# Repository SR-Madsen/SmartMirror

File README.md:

# SmartMirror
This project contains the KiCad and programming files used for a Smart Mirror project running Embedded Linux. The project is based on a microprocessor showing graphics and gathering data for showing information like weather and time.

## Project Structure
A block diagram of the project is shown in the figure below.

## Hardware
The hardware is based on the iMX6ULL microprocessor from NXP, with the design and PCB made myself, but inspired by evaluation kits.

## Software
The NXP Pins Tool is used for setting up the microprocessor. NXP's Embedded Linux tools are used for configuring the software.

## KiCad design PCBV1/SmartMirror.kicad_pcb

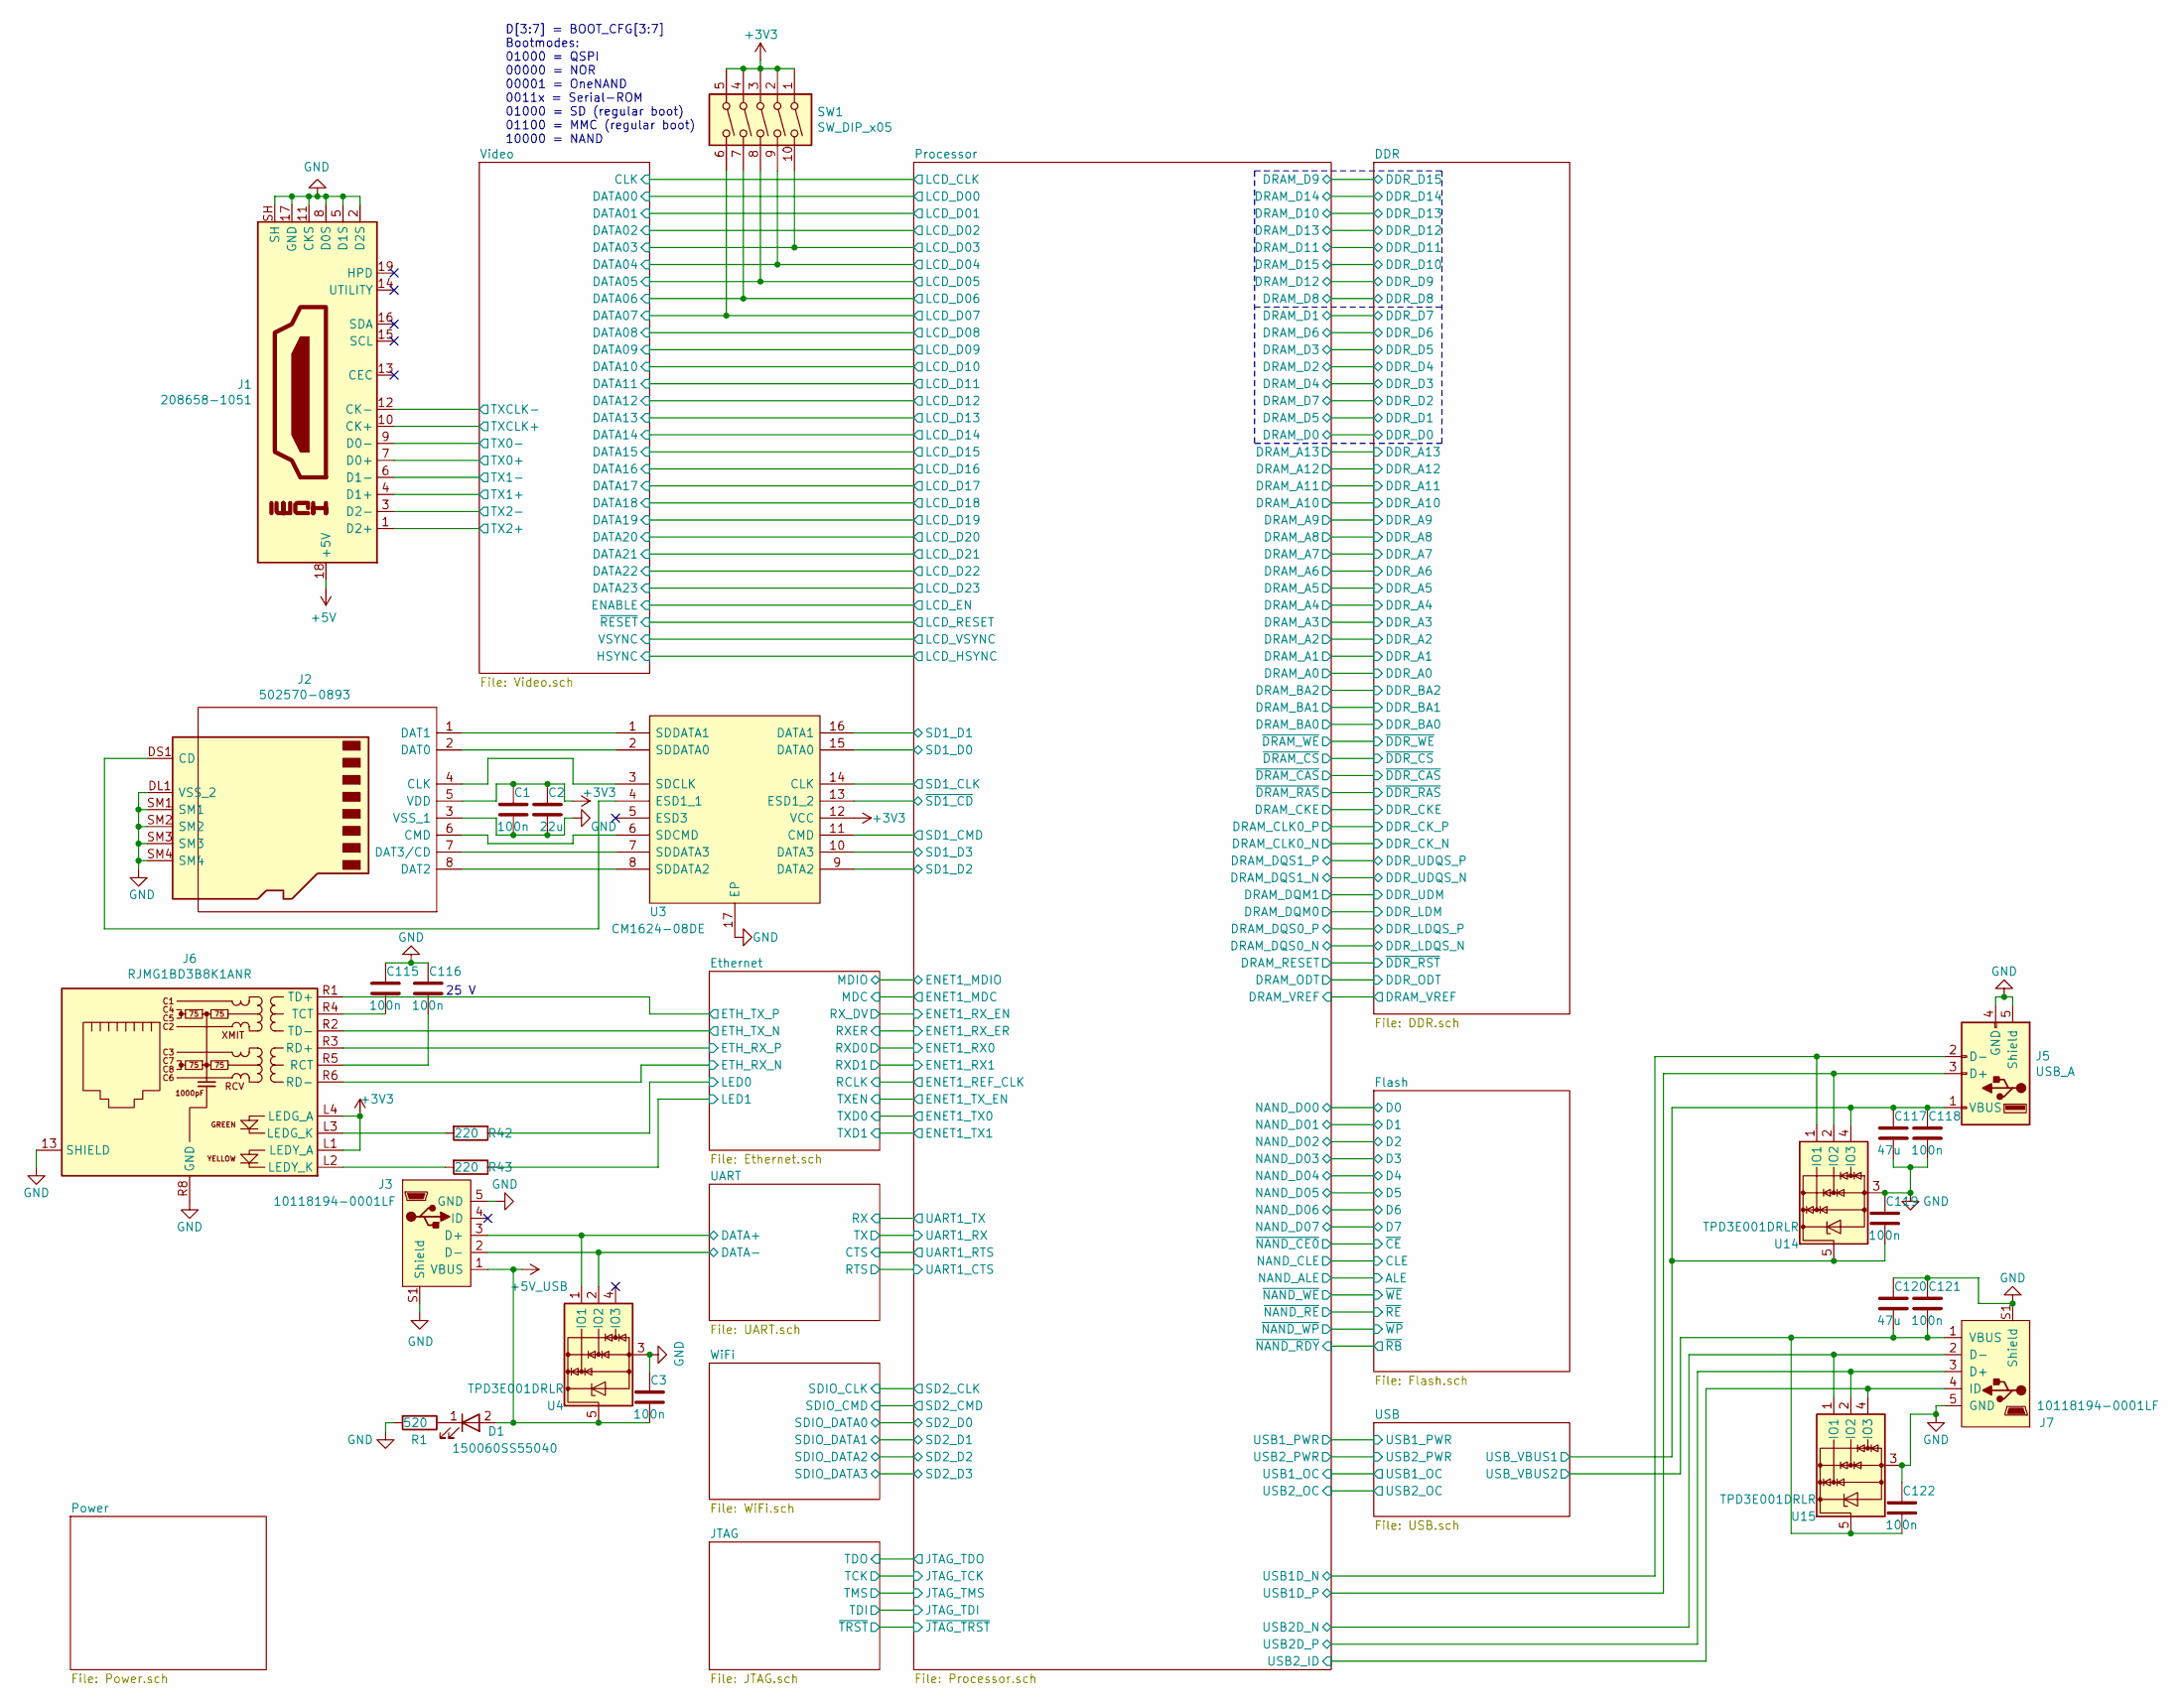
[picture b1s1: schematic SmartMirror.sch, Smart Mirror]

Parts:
C1, C3, C115, C116, C118, C119, C121, C122: 100n; C_0603_1608Metric
C2: 22u; C_0603_1608Metric
C117, C120: 47u; C_0805_2012Metric
D1: 150060SS55040; Mouser Part Number 710-150060SS55040
J1: 208658-1051; 2086581051
J2: 502570-0893
J3, J7: 10118194-0001LF
J5: USB_A; USB_A_Molex_67643_Horizontal
J6: RJMG1BD3B8K1ANR
R1: 520; R_0603_1608Metric
R42, R43: 220; R_0603_1608Metric
SW1: SW_DIP_x05; SW_DIP_SPSTx05_Slide_6.7x14.26mm_W6.73mm_P2.54mm_LowProfile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
U3: CM1624-08DE; CM1624
U4, U14, U15: TPD3E001DRLR; SOT-553

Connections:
+3V3: C1.1, C2.1, J2.5 (VDD), J6.L1 (LEDY_A), J6.L4 (LEDG_A), SW1.1, SW1.2, SW1.3, SW1.4, SW1.5, U3.12 (VCC); also elsewhere on the board
+5V: J1.18 (+5V); also elsewhere on the board
+5V_USB: C3.2, D1.2 (A), J3.1 (VBUS), U4.5; also elsewhere on the board
/Ethernet/ETH_RX_N: J6.R6 (RD-); also elsewhere on the board
/Ethernet/ETH_RX_P: J6.R3 (RD+); also elsewhere on the board
/Ethernet/ETH_TX_N: J6.R2 (TD-); also elsewhere on the board
/Ethernet/ETH_TX_P: J6.R1 (TD+); also elsewhere on the board
/Ethernet/LED0: R42.1; also elsewhere on the board
/Ethernet/LED1: R43.1; also elsewhere on the board
/Processor/SD1_CLK: U3.14 (CLK); also elsewhere on the board
/Processor/SD1_CMD: U3.11 (CMD); also elsewhere on the board
/Processor/SD1_D0: U3.15 (DATA0); also elsewhere on the board
/Processor/SD1_D1: U3.16 (DATA1); also elsewhere on the board
/Processor/SD1_D2: U3.9 (DATA2); also elsewhere on the board
/Processor/SD1_D3: U3.10 (DATA3); also elsewhere on the board
/Processor/USB1D_N: J5.2 (D-), U14.1 (IO1); also elsewhere on the board
/Processor/USB1D_P: J5.3 (D+), U14.2 (IO2); also elsewhere on the board
/Processor/USB2D_N: J7.2 (D-), U15.1 (IO1); also elsewhere on the board
/Processor/USB2D_P: J7.3 (D+), U15.2 (IO2); also elsewhere on the board
/Processor/USB2_ID: J7.4 (ID), U15.4 (IO3); also elsewhere on the board
/Processor/~SD1_CD: U3.13 (ESD1_2); also elsewhere on the board
/UART/DATA+: J3.3 (D+), U4.1 (IO1); also elsewhere on the board
/UART/DATA-: J3.2 (D-), U4.2 (IO2); also elsewhere on the board
/USB/USB_VBUS1: C117.1, C118.1, C119.2, J5.1 (VBUS), U14.4 (IO3), U14.5; also elsewhere on the board
/USB/USB_VBUS2: C120.2, C121.2, C122.2, J7.1 (VBUS), U15.5; also elsewhere on the board
/Video/DATA03: SW1.10; also elsewhere on the board
/Video/DATA04: SW1.9; also elsewhere on the board
/Video/DATA05: SW1.8; also elsewhere on the board
/Video/DATA06: SW1.7; also elsewhere on the board
/Video/DATA07: SW1.6; also elsewhere on the board
/Video/TX0+: J1.7 (D0+); also elsewhere on the board
/Video/TX0-: J1.9 (D0-); also elsewhere on the board
/Video/TX1+: J1.4 (D1+); also elsewhere on the board
/Video/TX1-: J1.6 (D1-); also elsewhere on the board
/Video/TX2+: J1.1 (D2+); also elsewhere on the board
/Video/TX2-: J1.3 (D2-); also elsewhere on the board
/Video/TXCLK+: J1.10 (CK+); also elsewhere on the board
/Video/TXCLK-: J1.12 (CK-); also elsewhere on the board
GND: C1.2, C2.2, C3.1, C115.1, C116.1, C117.2, C118.2, C119.1, C120.1, C121.1, C122.1, J1.2 (D2S), J1.5 (D1S), J1.8 (D0S), J1.11 (CKS), J1.17 (GND), J1.SH, J2.3 (VSS_1), J2.DL1 (VSS_2), J2.SM1, J2.SM2, J2.SM3, J2.SM4, J3.5 (GND), J3.S1 (Shield), J5.4 (GND), J5.5 (Shield), J6.13 (SHIELD), J6.R8 (GND), J7.5 (GND), J7.S1 (Shield), R1.2, U3.17 (EP), U4.3, U14.3, U15.3; also elsewhere on the board
unnamed: C115.2, J6.R4 (TCT)
unnamed: C116.2, J6.R5 (RCT)
unnamed: D1.1 (K), R1.1
unnamed: J2.1 (DAT1), U3.1 (SDDATA1)
unnamed: J2.2 (DAT0), U3.2 (SDDATA0)
unnamed: J2.4 (CLK), U3.3 (SDCLK)
unnamed: J2.6 (CMD), U3.6 (SDCMD)
unnamed: J2.7 (DAT3/CD), U3.7 (SDDATA3)
unnamed: J2.8 (DAT2), U3.8 (SDDATA2)
unnamed: J2.DS1 (CD), U3.4 (ESD1_1)
unnamed: J6.L2 (LEDY_K), R43.2
unnamed: J6.L3 (LEDG_K), R42.2

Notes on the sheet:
D[3:7] = BOOT_CFG[3:7] Bootmodes: 01000 = QSPI 00000 = NOR 00001 = OneNAND 0011x = Serial-ROM 01000 = SD (regular boot) 01100 = MMC (regular boot) 10000 = NAND
25 V

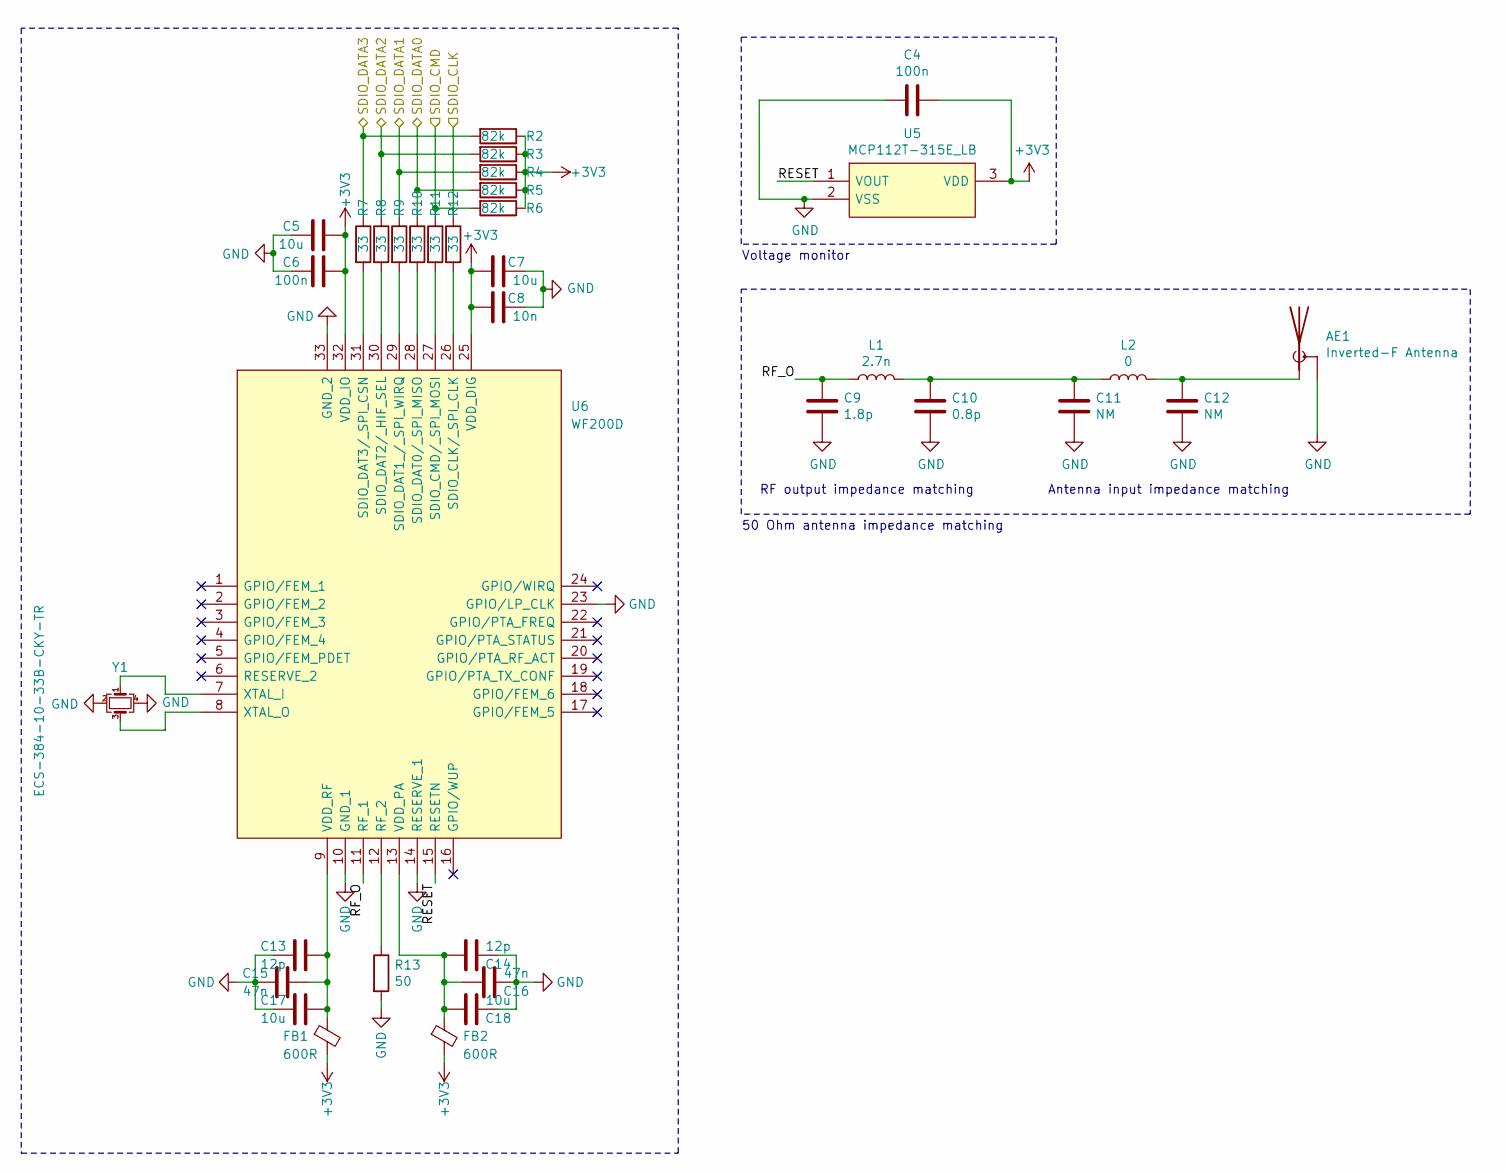
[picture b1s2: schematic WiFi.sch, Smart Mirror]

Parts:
AE1: Inverted-F Antenna; Texas_SWRA117D_2.4GHz_Left
C4, C6: 100n; C_0603_1608Metric
C5, C7, C17, C18: 10u; C_0603_1608Metric
C8: 10n; C_0603_1608Metric
C9: 1.8p; C_0402_1005Metric
C10: 0.8p; C_0402_1005Metric
C11, C12: NM; C_0402_1005Metric
C13, C14: 12p; C_0603_1608Metric
C15, C16: 47n; C_0603_1608Metric
FB1, FB2: 600R; L_0603_1608Metric
L1: 2.7n; L_0402_1005Metric
L2: 0; L_0402_1005Metric
R2, R3, R4, R5, R6: 82k; R_0603_1608Metric
R7, R8, R9, R10, R11, R12: 33; R_0603_1608Metric
R13: 50; R_0603_1608Metric
U5: MCP112T-315E_LB; MCP112T-315E-LB; Manufacturer_Part_Number MCP112T-315E/LB; Mouser Part Number 579-MCP112T-315E/LB
U6: WF200D
Y1: ECS-384-10-33B-CKY-TR; ECS3841033BCKYTR

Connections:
+3V3: C4.1, C5.1, C6.1, C7.2, C8.2, FB1.2, FB2.2, R2.1, R3.1, R4.1, R5.1, R6.1, U5.3 (VDD), U6.25 (VDD_DIG), U6.32 (VDD_IO); also elsewhere on the board
/Processor/SD2_CLK: R12.1; also elsewhere on the board
/Processor/SD2_CMD: R6.2, R11.1; also elsewhere on the board
/Processor/SD2_D0: R5.2, R10.1; also elsewhere on the board
/Processor/SD2_D1: R4.2, R9.1; also elsewhere on the board
/Processor/SD2_D2: R3.2, R8.1; also elsewhere on the board
/Processor/SD2_D3: R2.2, R7.1; also elsewhere on the board
/WiFi/RESET: U5.1 (VOUT), U6.15 (RESETN)
/WiFi/RF_O: C9.1, L1.1, U6.11 (RF_1)
GND: AE1.2 (Shield), C4.2, C5.2, C6.2, C7.1, C8.1, C9.2, C10.2, C11.2, C12.2, C13.2, C14.2, C15.2, C16.2, C17.2, C18.2, R13.2, U5.2 (VSS), U6.10 (GND_1), U6.14 (RESERVE_1), U6.23 (GPIO/LP_CLK), U6.33 (GND_2), Y1.2, Y1.4; also elsewhere on the board
unnamed: AE1.1 (A), C12.1, L2.2
unnamed: C10.1, C11.1, L1.2, L2.1
unnamed: C13.1, C15.1, C17.1, FB1.1, U6.9 (VDD_RF)
unnamed: C14.1, C16.1, C18.1, FB2.1, U6.13 (VDD_PA)
unnamed: R7.2, U6.31 (SDIO_DAT3/_SPI_CSN)
unnamed: R8.2, U6.30 (SDIO_DAT2/_HIF_SEL)
unnamed: R9.2, U6.29 (SDIO_DAT1_/_SPI_WIRQ)
unnamed: R10.2, U6.28 (SDIO_DAT0/_SPI_MISO)
unnamed: R11.2, U6.27 (SDIO_CMD/_SPI_MOSI)
unnamed: R12.2, U6.26 (SDIO_CLK/_SPI_CLK)
unnamed: R13.1, U6.12 (RF_2)
unnamed: U6.7 (XTAL_I), Y1.1
unnamed: U6.8 (XTAL_O), Y1.3

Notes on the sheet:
Voltage monitor
RF output impedance matching
Antenna input impedance matching
50 Ohm antenna impedance matching

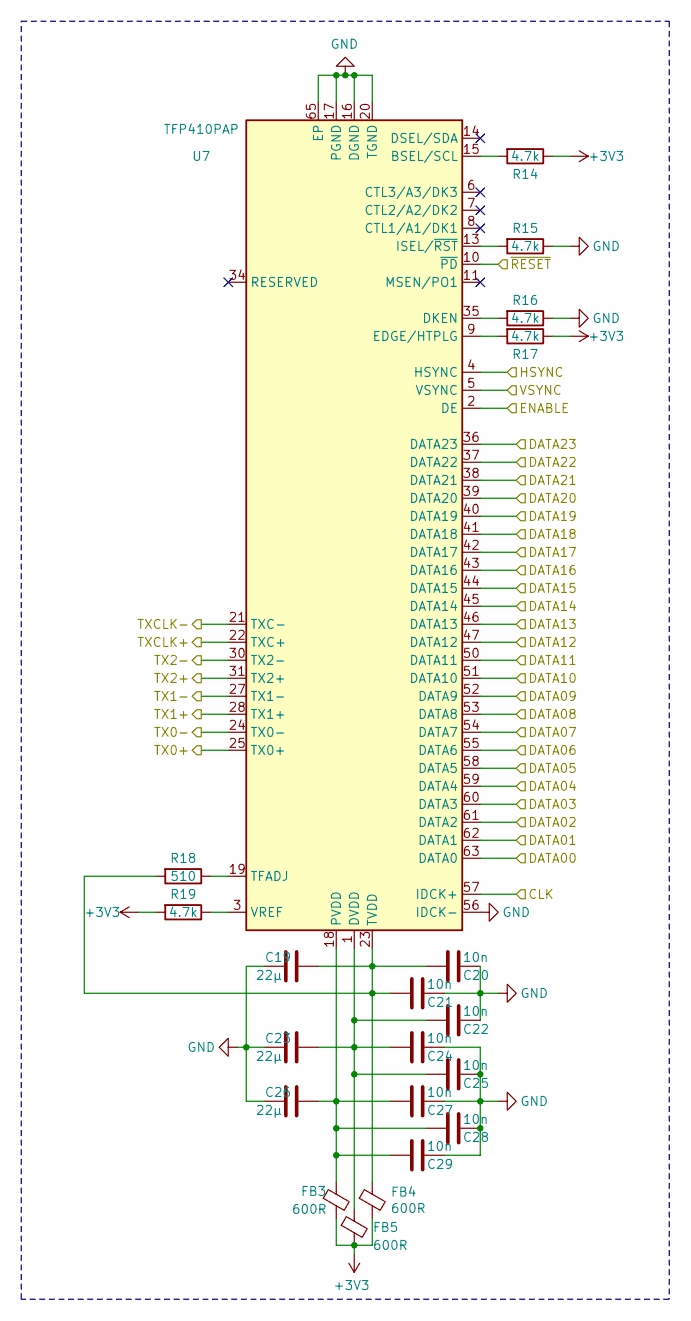
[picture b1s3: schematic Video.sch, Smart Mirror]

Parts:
C19, C23, C26: 22µ; C_0603_1608Metric
C20, C21, C22, C24, C25, C27, C28, C29: 10n; C_0603_1608Metric
FB3, FB4, FB5: 600R; L_0603_1608Metric
R14, R15, R16, R17, R19: 4.7k; R_0603_1608Metric
R18: 510; R_0603_1608Metric
U7: TFP410PAP; HTQFP-64-1EP_10x10mm_P0.5mm_EP8x8mm_Mask4.4x4.4mm_ThermalVi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

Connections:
+3V3: FB3.2, FB4.2, FB5.2, R14.1, R17.1, R19.2; also elsewhere on the board
/Processor/LCD_RESET: U7.10 (~PD); also elsewhere on the board
/Processor/LCD_VSYNC: U7.5 (VSYNC); also elsewhere on the board
/Video/CLK: U7.57 (IDCK+); also elsewhere on the board
/Video/DATA00: U7.63 (DATA0); also elsewhere on the board
/Video/DATA01: U7.62 (DATA1); also elsewhere on the board
/Video/DATA02: U7.61 (DATA2); also elsewhere on the board
/Video/DATA03: U7.60 (DATA3); also elsewhere on the board
/Video/DATA04: U7.59 (DATA4); also elsewhere on the board
/Video/DATA05: U7.58 (DATA5); also elsewhere on the board
/Video/DATA06: U7.55 (DATA6); also elsewhere on the board
/Video/DATA07: U7.54 (DATA7); also elsewhere on the board
/Video/DATA08: U7.53 (DATA8); also elsewhere on the board
/Video/DATA09: U7.52 (DATA9); also elsewhere on the board
/Video/DATA10: U7.51 (DATA10); also elsewhere on the board
/Video/DATA11: U7.50 (DATA11); also elsewhere on the board
/Video/DATA12: U7.47 (DATA12); also elsewhere on the board
/Video/DATA13: U7.46 (DATA13); also elsewhere on the board
/Video/DATA14: U7.45 (DATA14); also elsewhere on the board
/Video/DATA15: U7.44 (DATA15); also elsewhere on the board
/Video/DATA16: U7.43 (DATA16); also elsewhere on the board
/Video/DATA17: U7.42 (DATA17); also elsewhere on the board
/Video/DATA18: U7.41 (DATA18); also elsewhere on the board
/Video/DATA19: U7.40 (DATA19); also elsewhere on the board
/Video/DATA20: U7.39 (DATA20); also elsewhere on the board
/Video/DATA21: U7.38 (DATA21); also elsewhere on the board
/Video/DATA22: U7.37 (DATA22); also elsewhere on the board
/Video/DATA23: U7.36 (DATA23); also elsewhere on the board
/Video/ENABLE: U7.2 (DE); also elsewhere on the board
/Video/HSYNC: U7.4 (HSYNC); also elsewhere on the board
/Video/TX0+: U7.25 (TX0+); also elsewhere on the board
/Video/TX0-: U7.24 (TX0-); also elsewhere on the board
/Video/TX1+: U7.28 (TX1+); also elsewhere on the board
/Video/TX1-: U7.27 (TX1-); also elsewhere on the board
/Video/TX2+: U7.31 (TX2+); also elsewhere on the board
/Video/TX2-: U7.30 (TX2-); also elsewhere on the board
/Video/TXCLK+: U7.22 (TXC+); also elsewhere on the board
/Video/TXCLK-: U7.21 (TXC-); also elsewhere on the board
GND: C19.2, C20.1, C21.1, C22.1, C23.2, C24.1, C25.1, C26.2, C27.1, C28.1, C29.1, R15.1, R16.1, U7.16 (DGND), U7.17 (PGND), U7.20 (TGND), U7.26 (TGND), U7.32 (TGND), U7.48 (DGND), U7.56 (IDCK-), U7.64 (DGND), U7.65 (EP); also elsewhere on the board
unnamed: C19.1, C20.2, C21.2, FB4.1, R18.2, U7.23 (TVDD), U7.29 (TVDD)
unnamed: C22.2, C23.1, C24.2, C25.2, FB5.1, U7.1 (DVDD), U7.12 (DVDD), U7.33 (DVDD)
unnamed: C26.1, C27.2, C28.2, C29.2, FB3.1, U7.18 (PVDD)
unnamed: R14.2, U7.15 (BSEL/SCL)
unnamed: R15.2, U7.13 (ISEL/~RST)
unnamed: R16.2, U7.35 (DKEN)
unnamed: R17.2, U7.9 (EDGE/HTPLG)
unnamed: R18.1, U7.19 (TFADJ)
unnamed: R19.1, U7.3 (VREF)

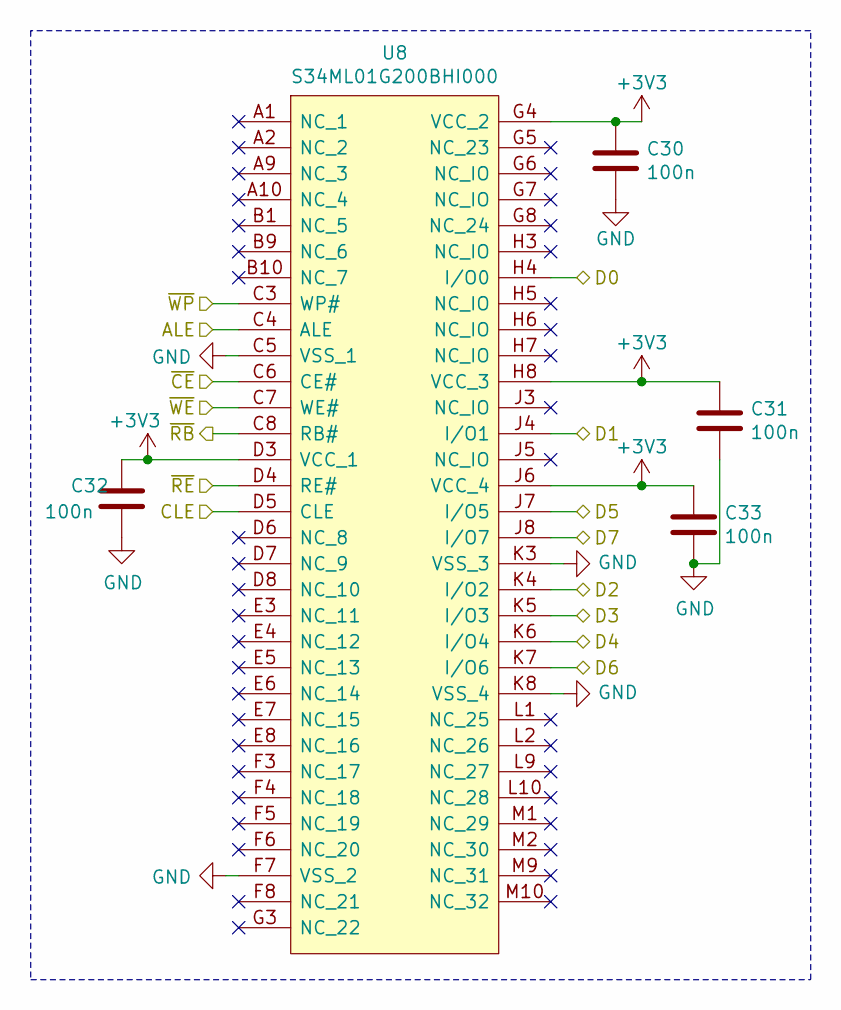
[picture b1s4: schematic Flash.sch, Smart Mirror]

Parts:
C30, C31, C32, C33: 100n; C_0603_1608Metric
U8: S34ML01G200BHI000

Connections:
+3V3: C30.1, C31.1, C32.1, C33.1, U8.D3 (VCC_1), U8.G4 (VCC_2), U8.H8 (VCC_3), U8.J6 (VCC_4); also elsewhere on the board
/Flash/ALE: U8.C4 (ALE); also elsewhere on the board
/Flash/CLE: U8.D5 (CLE); also elsewhere on the board
/Flash/D0: U8.H4 (I/O0); also elsewhere on the board
/Flash/D1: U8.J4 (I/O1); also elsewhere on the board
/Flash/D2: U8.K4 (I/O2); also elsewhere on the board
/Flash/D3: U8.K5 (I/O3); also elsewhere on the board
/Flash/D4: U8.K6 (I/O4); also elsewhere on the board
/Flash/D5: U8.J7 (I/O5); also elsewhere on the board
/Flash/D6: U8.K7 (I/O6); also elsewhere on the board
/Flash/D7: U8.J8 (I/O7); also elsewhere on the board
/Flash/~CE: U8.C6 (CE#); also elsewhere on the board
/Processor/~NAND_RDY: U8.C8 (RB#); also elsewhere on the board
/Processor/~NAND_RE: U8.D4 (RE#); also elsewhere on the board
/Processor/~NAND_WE: U8.C7 (WE#); also elsewhere on the board
/Processor/~NAND_WP: U8.C3 (WP#); also elsewhere on the board
GND: C30.2, C31.2, C32.2, C33.2, U8.C5 (VSS_1), U8.F7 (VSS_2), U8.K3 (VSS_3), U8.K8 (VSS_4); also elsewhere on the board

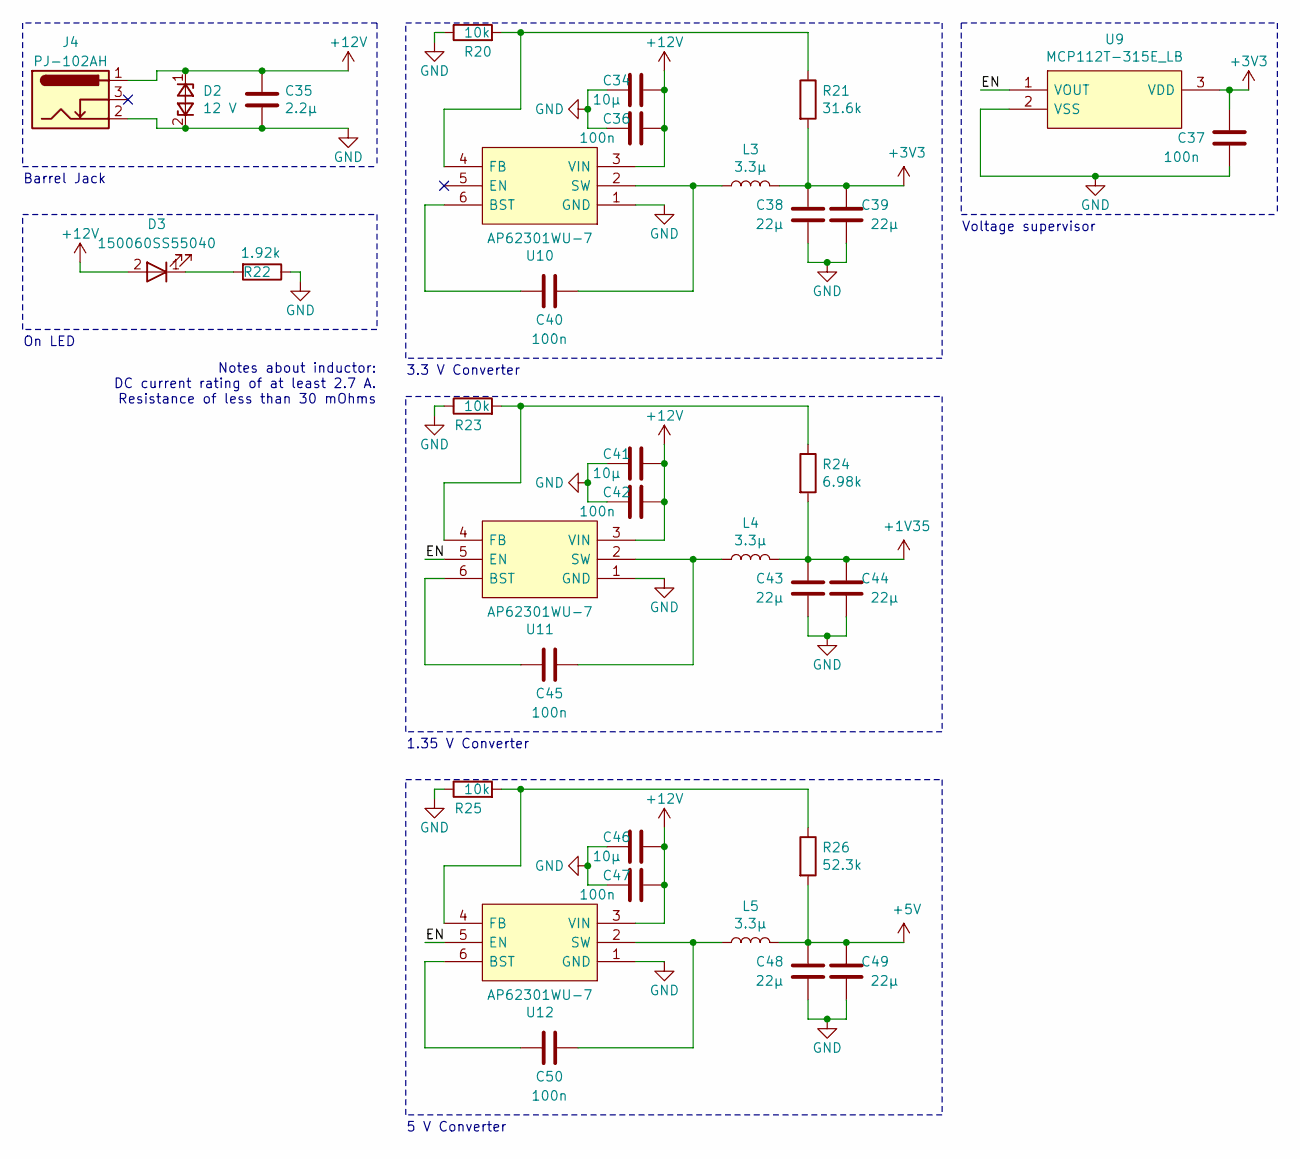
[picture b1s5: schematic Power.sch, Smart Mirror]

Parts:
C34, C41, C46: 10µ; C_0805_2012Metric
C35: 2.2µ; C_0805_2012Metric
C36, C37, C40, C42, C45, C47, C50: 100n; C_0603_1608Metric
C38, C39, C43, C44, C48, C49: 22µ; C_0603_1608Metric
D2: 12 V; PESD12VA-SFYL
D3: 150060SS55040; Mouser Part Number 710-150060SS55040
J4: PJ-102AH; BarrelJack_CUI_PJ-102AH_Horizontal
L3, L4, L5: 3.3µ; L_Taiyo-Yuden_NR-80xx
R20, R23, R25: 10k; R_0603_1608Metric
R21: 31.6k; R_0603_1608Metric
R22: 1.92k; R_0603_1608Metric
R24: 6.98k; R_0603_1608Metric
R26: 52.3k; R_0603_1608Metric
U9: MCP112T-315E_LB; MCP112T-315E-LB; Manufacturer_Part_Number MCP112T-315E/LB; Mouser Part Number 579-MCP112T-315E/LB
U10, U11, U12: AP62301WU-7; Manufacturer_Part_Number AP62301WU-7; Mouser Part Number 621-AP62301WU-7

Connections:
+1V35: C43.1, C44.1, L4.2, R24.2; also elsewhere on the board
+3V3: C37.1, C38.1, C39.1, L3.2, R21.2, U9.3 (VDD); also elsewhere on the board
+5V: C48.1, C49.1, L5.2, R26.2; also elsewhere on the board
+12V: C34.2, C35.1, C36.2, C41.2, C42.2, C46.2, C47.2, D2.1, D3.2 (A), J4.1, U10.3 (VIN), U11.3 (VIN), U12.3 (VIN)
/Power/EN: U9.1 (VOUT), U11.5 (EN), U12.5 (EN)
GND: C34.1, C35.2, C36.1, C37.2, C38.2, C39.2, C41.1, C42.1, C43.2, C44.2, C46.1, C47.1, C48.2, C49.2, D2.2, J4.2, R20.1, R22.1, R23.1, R25.1, U9.2 (VSS), U10.1 (GND), U11.1 (GND), U12.1 (GND); also elsewhere on the board
unnamed: C40.1, U10.6 (BST)
unnamed: C40.2, L3.1, U10.2 (SW)
unnamed: C45.1, U11.6 (BST)
unnamed: C45.2, L4.1, U11.2 (SW)
unnamed: C50.1, U12.6 (BST)
unnamed: C50.2, L5.1, U12.2 (SW)
unnamed: D3.1 (K), R22.2
unnamed: R20.2, R21.1, U10.4 (FB)
unnamed: R23.2, R24.1, U11.4 (FB)
unnamed: R25.2, R26.1, U12.4 (FB)

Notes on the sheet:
Barrel Jack
3.3 V Converter
Notes about inductor: DC current rating of at least 2.7 A. Resistance of less than 30 mOhms
1.35 V Converter
Voltage supervisor
On LED
5 V Converter

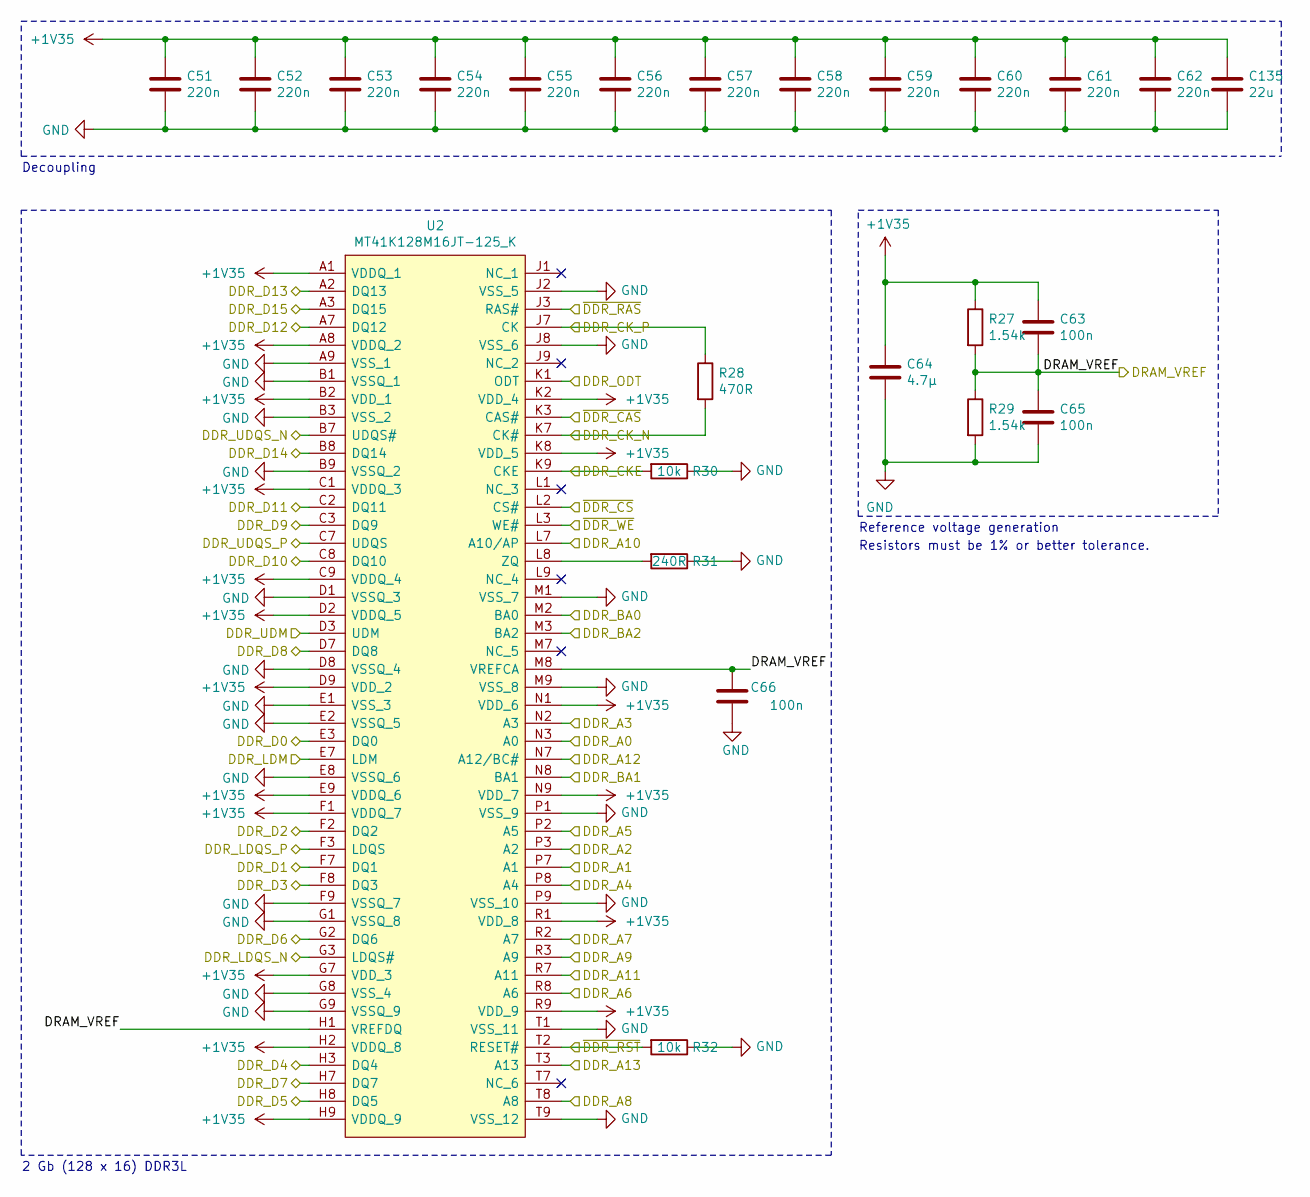
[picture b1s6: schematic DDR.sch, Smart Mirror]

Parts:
C51, C52, C53, C54, C55, C56, C57, C58, C59, C60, C61, C62: 220n; C_0402_1005Metric
C63, C65, C66: 100n; C_0402_1005Metric
C64: 4.7µ; C_0603_1608Metric
C135: 22u; C_0603_1608Metric
R27, R29: 1.54k; R_0402_1005Metric
R28: 470R; R_0402_1005Metric
R30, R32: 10k; R_0402_1005Metric
R31: 240R; R_0402_1005Metric
U2: MT41K128M16JT-125_K; MT41K128M16JT-125; Manufacturer_Part_Number MT41K128M16JT-125:K; Mouser Part Number 340-135795-TRAY

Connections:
+1V35: C51.1, C52.1, C53.1, C54.1, C55.1, C56.1, C57.1, C58.1, C59.1, C60.1, C61.1, C62.1, C63.1, C64.1, C135.1, R27.1, U2.A1 (VDDQ_1), U2.A8 (VDDQ_2), U2.B2 (VDD_1), U2.C1 (VDDQ_3), U2.C9 (VDDQ_4), U2.D2 (VDDQ_5), U2.D9 (VDD_2), U2.E9 (VDDQ_6), U2.F1 (VDDQ_7), U2.G7 (VDD_3), U2.H2 (VDDQ_8), U2.H9 (VDDQ_9), U2.K2 (VDD_4), U2.K8 (VDD_5), U2.N1 (VDD_6), U2.N9 (VDD_7), U2.R1 (VDD_8), U2.R9 (VDD_9); also elsewhere on the board
/DDR/DDR_A0: U2.N3 (A0); also elsewhere on the board
/DDR/DDR_A1: U2.P7 (A1); also elsewhere on the board
/DDR/DDR_A2: U2.P3 (A2); also elsewhere on the board
/DDR/DDR_A3: U2.N2 (A3); also elsewhere on the board
/DDR/DDR_A4: U2.P8 (A4); also elsewhere on the board
/DDR/DDR_A5: U2.P2 (A5); also elsewhere on the board
/DDR/DDR_A6: U2.R8 (A6); also elsewhere on the board
/DDR/DDR_A7: U2.R2 (A7); also elsewhere on the board
/DDR/DDR_A8: U2.T8 (A8); also elsewhere on the board
/DDR/DDR_A9: U2.R3 (A9); also elsewhere on the board
/DDR/DDR_A10: U2.L7 (A10/AP); also elsewhere on the board
/DDR/DDR_A11: U2.R7 (A11); also elsewhere on the board
/DDR/DDR_A12: U2.N7 (A12/BC#); also elsewhere on the board
/DDR/DDR_A13: U2.T3 (A13); also elsewhere on the board
/DDR/DDR_BA0: U2.M2 (BA0); also elsewhere on the board
/DDR/DDR_BA1: U2.N8 (BA1); also elsewhere on the board
/DDR/DDR_BA2: U2.M3 (BA2); also elsewhere on the board
/DDR/DDR_CKE: R30.2, U2.K9 (CKE); also elsewhere on the board
/DDR/DDR_CK_N: R28.2, U2.K7 (CK#); also elsewhere on the board
/DDR/DDR_CK_P: R28.1, U2.J7 (CK); also elsewhere on the board
/DDR/DDR_D0: U2.E3 (DQ0); also elsewhere on the board
/DDR/DDR_D1: U2.F7 (DQ1); also elsewhere on the board
/DDR/DDR_D2: U2.F2 (DQ2); also elsewhere on the board
/DDR/DDR_D3: U2.F8 (DQ3); also elsewhere on the board
/DDR/DDR_D4: U2.H3 (DQ4); also elsewhere on the board
/DDR/DDR_D5: U2.H8 (DQ5); also elsewhere on the board
/DDR/DDR_D6: U2.G2 (DQ6); also elsewhere on the board
/DDR/DDR_D7: U2.H7 (DQ7); also elsewhere on the board
/DDR/DDR_D8: U2.D7 (DQ8); also elsewhere on the board
/DDR/DDR_D9: U2.C3 (DQ9); also elsewhere on the board
/DDR/DDR_D10: U2.C8 (DQ10); also elsewhere on the board
/DDR/DDR_D11: U2.C2 (DQ11); also elsewhere on the board
/DDR/DDR_D12: U2.A7 (DQ12); also elsewhere on the board
/DDR/DDR_D13: U2.A2 (DQ13); also elsewhere on the board
/DDR/DDR_D14: U2.B8 (DQ14); also elsewhere on the board
/DDR/DDR_D15: U2.A3 (DQ15); also elsewhere on the board
/DDR/DDR_LDM: U2.E7 (LDM); also elsewhere on the board
/DDR/DDR_LDQS_N: U2.G3 (LDQS#); also elsewhere on the board
/DDR/DDR_LDQS_P: U2.F3 (LDQS); also elsewhere on the board
/DDR/DDR_ODT: U2.K1 (ODT); also elsewhere on the board
/DDR/DDR_UDM: U2.D3 (UDM); also elsewhere on the board
/DDR/DDR_UDQS_N: U2.B7 (UDQS#); also elsewhere on the board
/DDR/DDR_UDQS_P: U2.C7 (UDQS); also elsewhere on the board
/DDR/DRAM_VREF: C63.2, C65.1, C66.2, R27.2, R29.1, U2.H1 (VREFDQ), U2.M8 (VREFCA); also elsewhere on the board
/DDR/~DDR_CAS: U2.K3 (CAS#); also elsewhere on the board
/DDR/~DDR_CS: U2.L2 (CS#); also elsewhere on the board
/DDR/~DDR_RAS: U2.J3 (RAS#); also elsewhere on the board
/DDR/~DDR_WE: U2.L3 (WE#); also elsewhere on the board
/Processor/DRAM_RESET: R32.2, U2.T2 (RESET#); also elsewhere on the board
GND: C51.2, C52.2, C53.2, C54.2, C55.2, C56.2, C57.2, C58.2, C59.2, C60.2, C61.2, C62.2, C64.2, C65.2, C66.1, C135.2, R29.2, R30.1, R31.1, R32.1, U2.A9 (VSS_1), U2.B1 (VSSQ_1), U2.B3 (VSS_2), U2.B9 (VSSQ_2), U2.D1 (VSSQ_3), U2.D8 (VSSQ_4), U2.E1 (VSS_3), U2.E2 (VSSQ_5), U2.E8 (VSSQ_6), U2.F9 (VSSQ_7), U2.G1 (VSSQ_8), U2.G8 (VSS_4), U2.G9 (VSSQ_9), U2.J2 (VSS_5), U2.J8 (VSS_6), U2.M1 (VSS_7), U2.M9 (VSS_8), U2.P1 (VSS_9), U2.P9 (VSS_10), U2.T1 (VSS_11), U2.T9 (VSS_12); also elsewhere on the board
unnamed: R31.2, U2.L8 (ZQ)

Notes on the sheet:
Resistors must be 1% or better tolerance.
2 Gb (128 x 16) DDR3L
Decoupling
Reference voltage generation

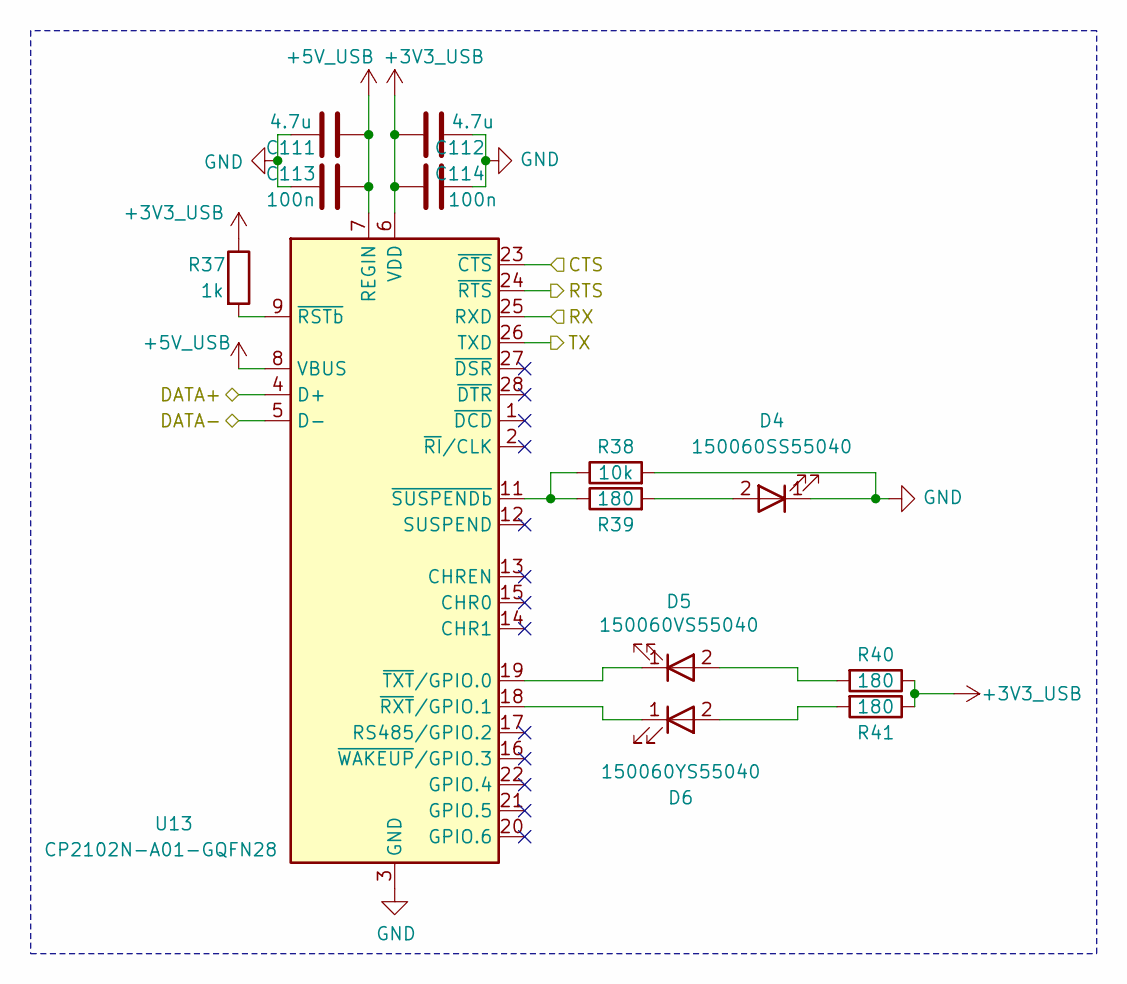
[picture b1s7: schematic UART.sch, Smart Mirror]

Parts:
C111, C112: 4.7u; C_0603_1608Metric
C113, C114: 100n; C_0603_1608Metric
D4: 150060SS55040; Mouser Part Number 710-150060SS55040
D5: 150060VS55040; 150060SS55040; Mouser Part Number 710-150060VS55040
D6: 150060YS55040; 150060SS55040; Mouser Part Number 710-150060YS55040
R37: 1k; R_0603_1608Metric
R38: 10k; R_0603_1608Metric
R39, R40, R41: 180; R_0603_1608Metric
U13: CP2102N-A01-GQFN28; QFN-28-1EP_5x5mm_P0.5mm_EP3.35x3.35mm

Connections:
+3V3_USB: C112.2, C114.2, R37.1, R40.1, R41.1, U13.6 (VDD)
+5V_USB: C111.1, C113.1, U13.7 (REGIN), U13.8 (VBUS); also elsewhere on the board
/UART/CTS: U13.23 (~CTS); also elsewhere on the board
/UART/DATA+: U13.4 (D+); also elsewhere on the board
/UART/DATA-: U13.5 (D-); also elsewhere on the board
/UART/RTS: U13.24 (~RTS); also elsewhere on the board
/UART/RX: U13.25 (RXD); also elsewhere on the board
/UART/TX: U13.26 (TXD); also elsewhere on the board
GND: C111.2, C112.1, C113.2, C114.1, D4.1 (K), R38.2, U13.3 (GND), U13.29 (GND); also elsewhere on the board
unnamed: D4.2 (A), R39.2
unnamed: D5.1 (K), U13.19 (~TXT~/GPIO.0)
unnamed: D5.2 (A), R40.2
unnamed: D6.1 (K), U13.18 (~RXT~/GPIO.1)
unnamed: D6.2 (A), R41.2
unnamed: R37.2, U13.9 (~RSTb)
unnamed: R38.1, R39.1, U13.11 (~SUSPENDb)
